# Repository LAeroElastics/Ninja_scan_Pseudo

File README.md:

Ninja_scan_Pseudo
=================

Very small IMU+GPS logger(gonna add some description later)

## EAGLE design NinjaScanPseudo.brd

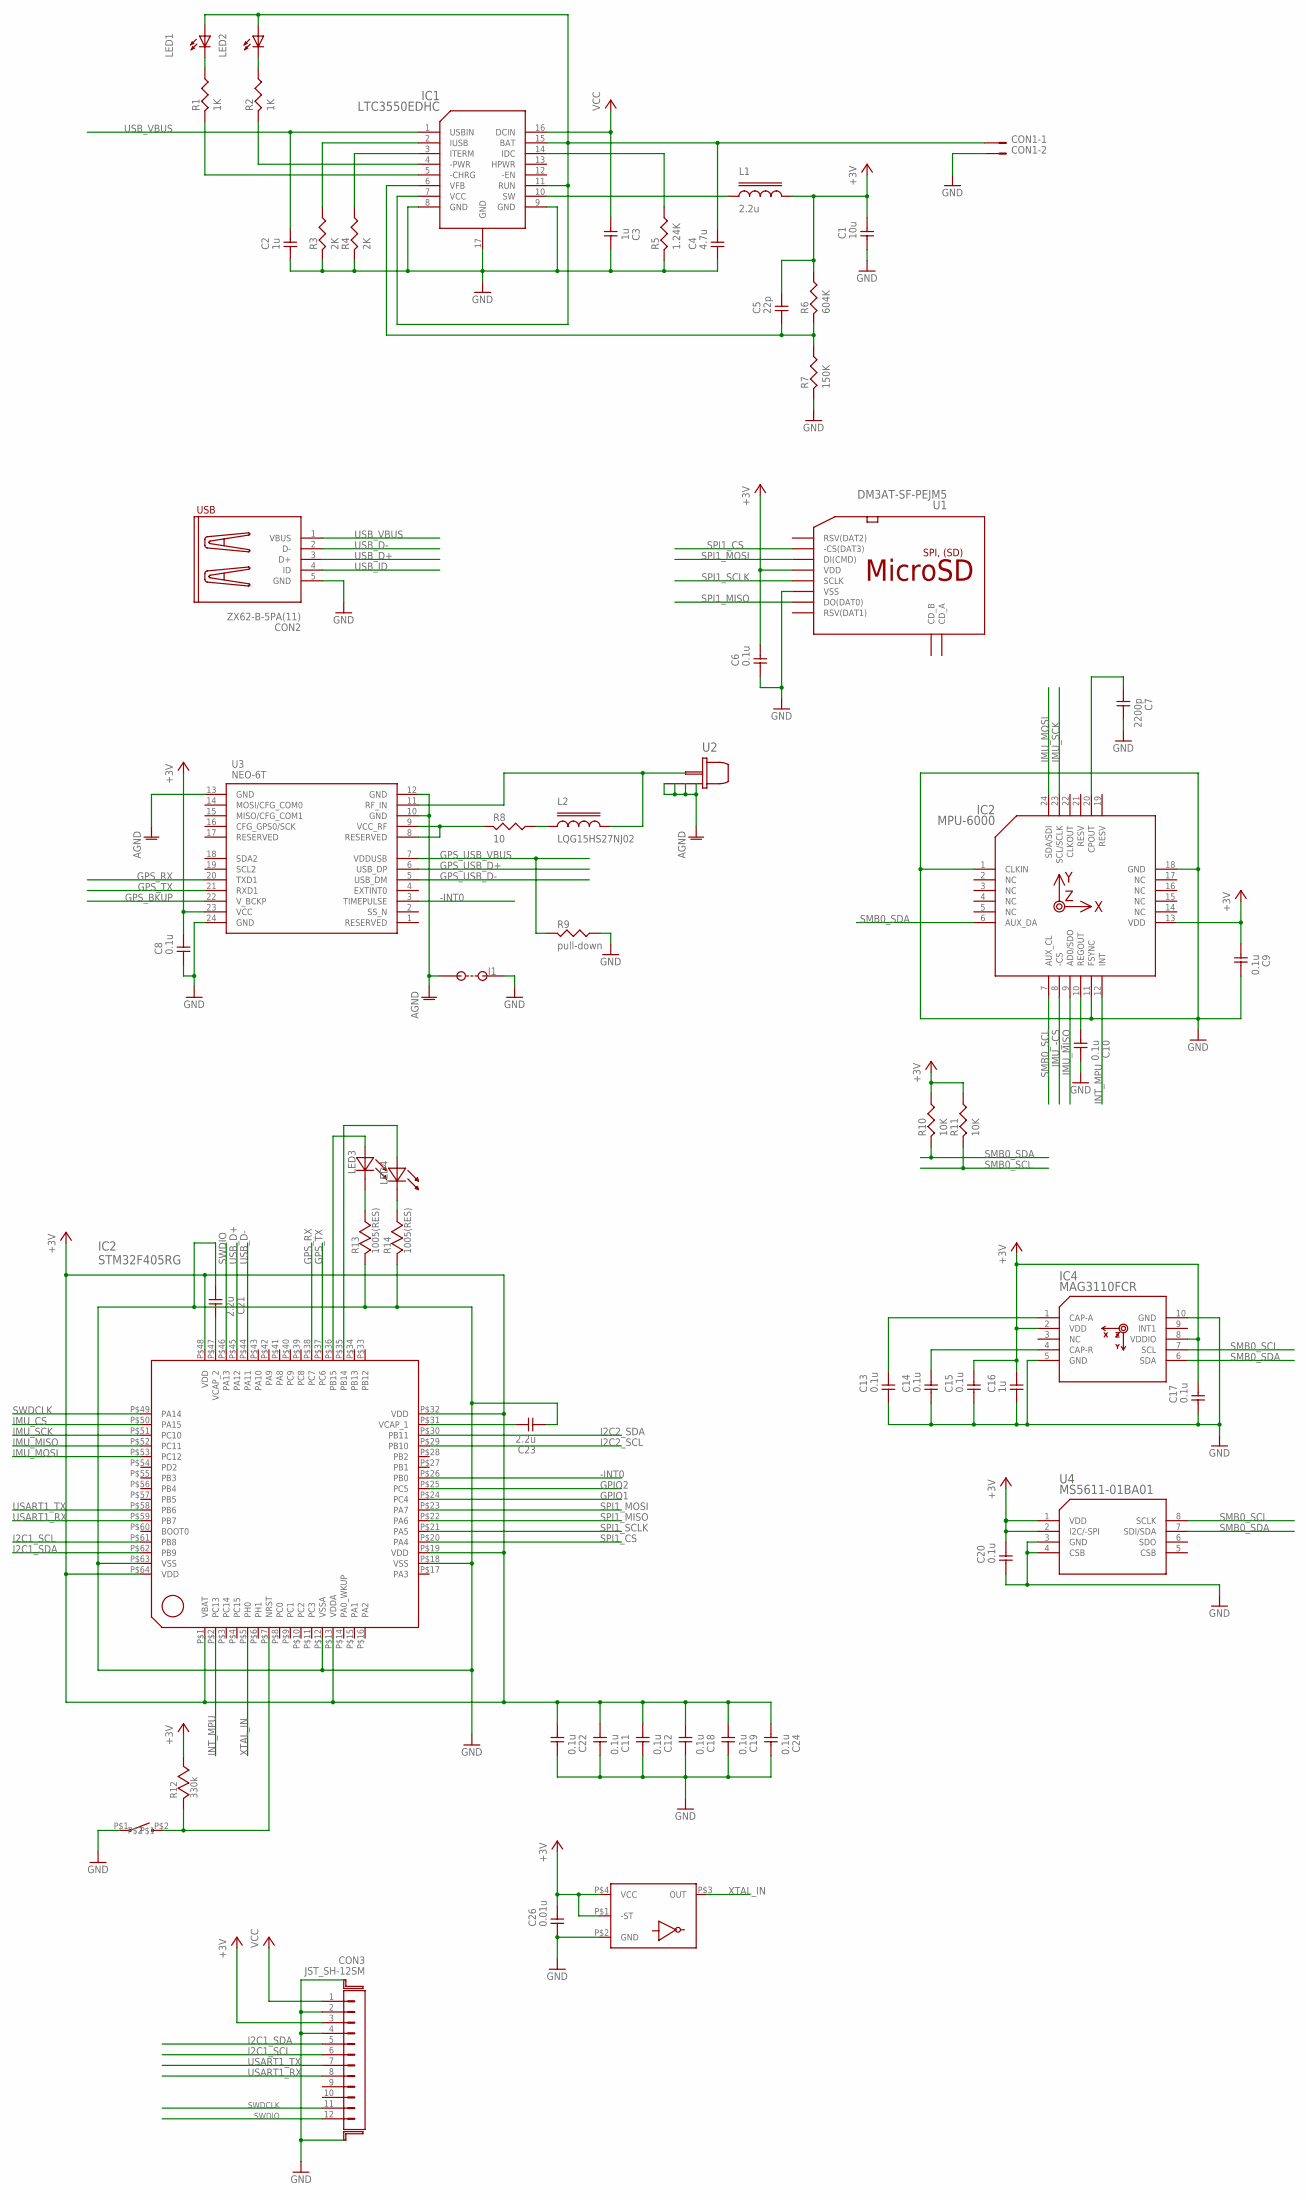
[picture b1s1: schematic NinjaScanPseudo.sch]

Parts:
C1: 10u; 3216
C2, C3, C16: 1u; 1005
C4: 4.7u; 2012
C5: 22p; 1005
C6, C8, C9, C10, C11, C12, C13, C14, C15, C17, C18, C19, C20, C22, C24: 0.1u; 1005
C7: 2200p; 1005
C21, C23: 2.2u; 1005
C26: 0.01u; 1005
CON1: JST_ZH-2B(MM)
CON2: ZX62-B-5PA(11); ZX62-AB-5PA
CON3: JST_SH-12SM; JST_SH-SM12B
IC1: LTC3550EDHC; DFN16BP
IC2: MPU-6000; QFN24
IC4: MAG3110FCR; DFN10
J1: JUMPER1608; 1608
L1: 2.2u; 3225
L2: LQG15HS27NJ02; 1005
LED1, LED2: LED1608; 1608D
LED3: LED3; 1608
LED4: 1608(LED); 1608
R1, R2: 1K; 1005
R3, R4: 2K; 1005
R5: 1.24K; 1005
R6: 604K; 1005
R7: 150K; 1005
R8: 10; 1005
R9: pull-down; 1005
R10, R11: 10K; 1005
R12: 330k; 1005
R13, R14: 1005(RES); 1005
U1: DM3AT-SF-PEJM5; DM3
U2: H.FL
U3: NEO-6T; NEO
U4: MS5611-01BA01; LGA8
U$6: STM32F405_64; TQFP-64
U$8: OMRON_B3U_1000P; B3U_1000P
U$15: SG-210; EPSON_2.5X2.0X0.8MM

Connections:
+3V: C1.2, C5.P$2 (2), C6.P$2 (2), C8.P$2 (2), C9.P$1 (1), C11.P$1 (1), C12.P$1 (1), C15.P$2 (2), C16.P$2 (2), C17.P$2 (2), C18.P$1 (1), C19.P$1 (1), C20.P$2 (2), C22.P$1 (1), C24.P$1 (1), C26.P$2 (2), CON3.3, IC2.13 (VDD), IC4.2 (VDD), IC4.8 (VDDIO), L1.2, R6.P$1 (1), R10.P$1 (1), R11.P$1 (1), R12.P$2 (2), U1.4 (VDD), U3.23 (VCC), U4.1 (VDD), U4.2 (I2C/-SPI), U$6.P$1 (VBAT), U$6.P$13 (VDDA), U$6.P$19 (VDD), U$6.P$32 (VDD), U$6.P$48 (VDD), U$6.P$64 (VDD), U$15.P$1 (-ST), U$15.P$4 (VCC)
-INT0: U3.3 (TIMEPULSE), U$6.P$26 (PB0)
AGND: J1.P$1, U2.GND@1 (GND), U2.GND@2 (GND), U2.GND@3 (GND), U3.10 (GND), U3.12 (GND), U3.13 (GND)
GND: C1.1, C2.P$1 (1), C3.P$2 (2), C4.1, C6.P$1 (1), C7.P$2 (2), C8.P$1 (1), C9.P$2 (2), C10.P$2 (2), C11.P$2 (2), C12.P$2 (2), C13.P$1 (1), C14.P$1 (1), C15.P$1 (1), C16.P$1 (1), C17.P$1 (1), C18.P$2 (2), C19.P$2 (2), C20.P$1 (1), C21.P$1 (1), C22.P$2 (2), C23.P$1 (1), C24.P$2 (2), C26.P$1 (1), CON1.2, CON2.5 (GND), CON2.GUIDE@L1 (GND), CON2.GUIDE@L3 (GND), CON2.GUIDE@R1 (GND), CON2.GUIDE@R3 (GND), CON3.2, CON3.4, CON3.GUIDE@L (GUIDE), CON3.GUIDE@R (GUIDE), IC1.8 (GND), IC1.9 (GND), IC1.17 (GND), IC2.1 (CLKIN), IC2.11 (FSYNC), IC2.18 (GND), IC4.5 (GND), IC4.10 (GND), J1.P$2, R3.P$2 (2), R4.P$2 (2), R5.P$2 (2), R7.P$2 (2), R9.P$1 (1), R13.P$1 (1), R14.P$1 (1), U1.6 (VSS), U1.GND@1 (GND), U1.GND@2 (GND), U1.GND@3 (GND), U1.GND@4 (GND), U3.24 (GND), U4.3 (GND), U4.4 (CSB), U$6.P$12 (VSSA), U$6.P$18 (VSS), U$6.P$63 (VSS), U$8.P$1, U$15.P$2 (GND)
GPIO1: U$6.P$24 (PC4)
GPIO2: U$6.P$25 (PC5)
GPS_BKUP: U3.22 (V_BCKP)
GPS_RX: U3.20 (TXD1), U$6.P$38 (PC7)
GPS_TX: U3.21 (RXD1), U$6.P$37 (PC6)
GPS_USB_D+: U3.6 (USB_DP)
GPS_USB_D-: U3.5 (USB_DM)
GPS_USB_VBUS: R9.P$2 (2), U3.7 (VDDUSB)
I2C1_SCL: CON3.6, U$6.P$61 (PB8)
I2C1_SDA: CON3.5, U$6.P$62 (PB9)
I2C2_SCL: U$6.P$29 (PB10)
I2C2_SDA: U$6.P$30 (PB11)
IMU_-CS: IC2.8 (-CS)
IMU_CS: U$6.P$50 (PA15)
IMU_MISO: IC2.9 (AD0/SDO), U$6.P$52 (PC11)
IMU_MOSI: IC2.24 (SDA/SDI), U$6.P$53 (PC12)
IMU_SCK: IC2.23 (SCL/SCLK), U$6.P$51 (PC10)
INT_MPU: IC2.12 (INT), U$6.P$2 (PC13)
unnamed: C10.P$1 (1), IC2.10 (REGOUT)
unnamed: C23.P$2 (2), U$6.P$31 (VCAP_1)
unnamed: C7.P$1 (1), IC2.20 (CPOUT)
unnamed: LED4.P$1, U$6.P$35 (PB14)
unnamed: LED3.P$2, R13.P$2 (2)
unnamed: L2.P$1 (1), R8.P$1 (1)
unnamed: L2.P$2 (2), U2.SIG (C), U3.11 (RF_IN)
unnamed: R8.P$2 (2), U3.8 (RESERVED), U3.9 (VCC_RF)
unnamed: LED1.K, R1.P$1 (1)
unnamed: LED4.P$2, R14.P$2 (2)
unnamed: LED2.K, R2.P$1 (1)
unnamed: IC1.2 (IUSB), R3.P$1 (1)
unnamed: IC1.3 (ITERM), R4.P$1 (1)
unnamed: IC1.14 (IDC), R5.P$1 (1)
unnamed: C5.P$1 (1), IC1.6 (VFB), R6.P$2 (2), R7.P$1 (1)
unnamed: IC1.5 (-CHRG), R1.P$2 (2)
unnamed: IC1.10 (SW), L1.1
unnamed: IC1.4 (-PWR), R2.P$2 (2)
unnamed: C4.2, CON1.1, IC1.7 (VCC), IC1.11 (RUN), IC1.15 (BAT), LED1.A, LED2.A
unnamed: LED3.P$1, U$6.P$36 (PB15)
unnamed: R12.P$1 (1), U$6.P$7 (NRST), U$8.P$2
unnamed: C13.P$2 (2), IC4.1 (CAP-A)
unnamed: C14.P$2 (2), IC4.4 (CAP-R)
unnamed: C21.P$2 (2), U$6.P$47 (VCAP_2)
SMB0_SCL: IC2.7 (AUX_CL), IC4.7 (SCL), R11.P$2 (2), U4.8 (SCLK)
SMB0_SDA: IC2.6 (AUX_DA), IC4.6 (SDA), R10.P$2 (2), U4.7 (SDI/SDA)
SPI1_CS: U1.2 (-CS(DAT3)), U$6.P$20 (PA4)
SPI1_MISO: U1.7 (DO(DAT0)), U$6.P$22 (PA6)
SPI1_MOSI: U1.3 (DI(CMD)), U$6.P$23 (PA7)
SPI1_SCLK: U1.5 (SCLK), U$6.P$21 (PA5)
SWDCLK: CON3.11, U$6.P$49 (PA14)
SWDIO: CON3.12, U$6.P$46 (PA13)
USART1_RX: CON3.8, U$6.P$59 (PB7)
USART1_TX: CON3.7, U$6.P$58 (PB6)
USB_D+: CON2.3 (D+), U$6.P$45 (PA12)
USB_D-: CON2.2 (D-), U$6.P$44 (PA11)
USB_ID: CON2.4 (ID)
USB_VBUS: C2.P$2 (2), CON2.1 (VBUS), IC1.1 (USBIN)
VCC: C3.P$1 (1), CON3.1, IC1.16 (DCIN)
XTAL_IN: U$6.P$5 (PH0), U$15.P$3 (OUT)

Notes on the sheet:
IC2 STM32F405RG

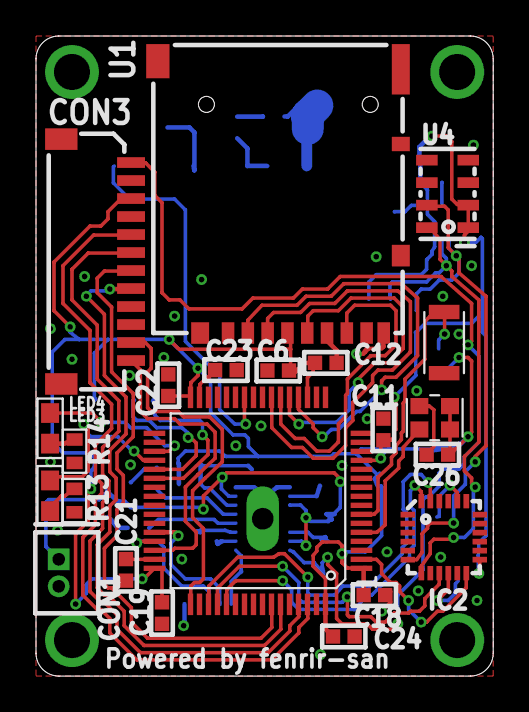
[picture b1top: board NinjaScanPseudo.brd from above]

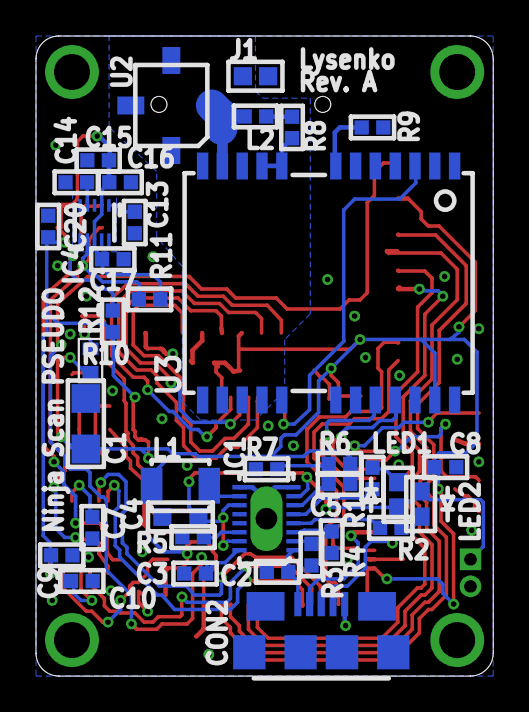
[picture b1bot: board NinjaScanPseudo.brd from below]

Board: 2 copper layers, 25.4 x 35.6 mm, 59 parts (37 on the bottom side), 52 nets.

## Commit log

2014-08-06 Added schematic and board
2014-08-08 some wiring issues were fixed.
2014-08-17 Minor update
2014-08-17 Bug fixed
2014-08-18 Silk added
2014-08-19 XTAL added
2014-08-20 CMOS Xtal added
2014-08-23 Final update of Rev.A
